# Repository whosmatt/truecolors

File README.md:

> [!CAUTION]
> This is not a manual! This repository serves as documentation only, use at your own risk.

# truecolors

This project captures a lot of embedded approaches I have picked up over the years and serves as my main ESP-IDF reference template for new projects that involve an embedded web UI w/ provisioning and OTA. 

Wide color gamut RGB Laser Mood Light  

I designed this light after growing fascinated with wide color gamut (110% BT.2020) rgb laser projectors. The colors are more vibrant and saturated than anything else. Even the best OLED screens look orange in comparison to the deep red produced by the almost monochromatic lasers.  
I got my hands on a Nichia NUMB12 Laser module, a very common module used in low to mid-tier RGB laser projectors.  
Unfortunately, the module is challenging to drive:
- Common cathode rules out most buck drivers which rely on a cathode shunt
- Forward voltage is very different between the green and red/blue channels
- Laser diodes are much more sensitive to overcurrent than LEDs
- The common cathode has a lower rating than the combined maximum currents, so staggered PWM is required to stay within the ratings

Beyond color gamut, this project also focuses on advanced audio reactive effects. Frustrated with RMS multiband effects, I trained a model to predict the presence and offset of beats in live audio, along with tagging drum hits.  
This allows effects to be completely locked into the tempo of a track rather than responding to volume changes. [truecolors-ml repo](https://github.com/whosmatt/truecolors-ml)

## Safety warning

The laser module used is a class 4 laser, with the output wavelength fully in the visible range. This means that the light has maximum eye damage potential and requires a robust safety protocol to be used safely. Use rated laser safety glasses and a shuttered room when testing without diffusers.

### Diffuser safety

I extensively tested the PLEXIGLAS® LED, Clear 0M200 SC diffuser material to ensure that it doesn't degrade under the intense laser light. Other diffuser materials **did** degrade and even slowly deform under the heat. High transmission is a must to minimize local heating, and the diffuser particles need to be the right size to ensure even diffusion across all three channels. Cheap diffusers may have a insufficient particle size, leading to a partially undiffused red beam passing straight through. Don't assume anything, test everything!

The diffuser design **must** include redundancy to ensure that the detachment/failure of a single diffuser does not compromise eye safety.

All fasteners relevant to eye safety must be secured with thread locker. Consider an additional hardware interlock.

## Hardware design

### PCB

A 4-Layer PCB was designed using Kicad 10. 4 layers were chosed to simplify USB 2.0 impedance and reduce laser driver EMI. Hierarchical design was used to keep the project organized, with Kicad's multichannel feature duplicating the laser driver layout. 

### MCU

An ESP32-S3 was chosen as the main controller for this project. It has plenty of power and the USB2.0 capability simplifies the design.  

ESP-IDF was used as the firmware framework, utilizing the rich scheduling and real-time capabilities of FreeRTOS.  
While most of my other projects rely on PlatformIO for toolchain management, I chose to use the official Espressif path for this to have more direct control over the build process.

### Power supply

USB C PD is used to power the design, with active negotiation to 20V/3A (bootstrapped by hardware and controlled by firmware).

### Laser driver

This design uses a customized constant off-time buck driver using the LM3409 switching converter IC. The design is common for all three channels and current is tuned by a multiturn potentiometer.  
COFT ensures known ripple amplitude, allowing the design to use minimal capacitance while staying safely within the laser's ratings.

Staggered PWM using the ESP32's MCPWM peripheral ensures that no two channels are on at the same time. An optional stretch parameters allows the channels to grow into the unused off time up to 100% combined duty with any color. This allows far higher brightness than with traditional staggered PWM.  
No gap was configured since the common cathode constraint is a thermal one, not an electrical one. 

### Temperature management

A heatpipe based server CPU cooler is used in conjunction with a Honeywell PTM7950 phase change thermal pad to keep the laser module cool.

A fine-adjustable 4-pin PWM server fan allows silent cooling with fine temperature control. This is important because the red laser diode array has a derating both above and below 45°C. The fan is PID controlled via the NTC thermistor located on the laser module.  
The tach signal is fed back to the MCU for fault monitoring. 

### Audio

A MSM261DGT003 PDM MEMS microphone is included for audio reactive effects. Connected to the ESP32's I2S peripheral in PDM mode.

A short recording was analyzed for coil whine cancellation: A single comb filter at the MCPWM frequency as well as a ~48db/oct 4kHz lowpass provided good results and leaves plenty of signal for audio reactive effects.

The first design was quite noisy, these mitigations have been tested and are already in the files:
- Lower noise inductors
  - C22396364 is footprint compatible and advertised as "ultra low buzz noise"
  - Small impact, because MLCC noise is dominant
- No output caps
  - With no output caps noise is reduced to a minimum
    Noise is still significantly audible at 240, 480 Hz. 120 Hz recommended
  - Requires carefully trimming to peak current via scope instead of average current
  - degraded EMI

The following hasn't been tested but is recommended:
- Low noise input caps
  - Murata ZRB: Drop in replacement with ~15dB reduction
  - Next board revision should allow for KRM series with ~25dB reduction

## Software design

### Audio

Core 1 is reserved for audio (including inference) and effect rendering.  

<details>
<summary>Audio pipeline diagram</summary>

```mermaid
flowchart TD
    MIC["PDM mic<br/>I2S RX, 48 kHz"] --> BLK["512-sample block<br/>93.75 blocks/s"]

    subgraph CORE1A["audio task: core 1, prio 5"]
        BLK --> FE["fe_block (frontend v2)<br/>DC block → 4 kHz hi-cut<br/>→ band split → multiband AGC"]
        BLK --> MEL["melflux_block<br/>1024 Hann (previous + current block)<br/>→ FFT → 16 mel bands 150 Hz - 4 kHz<br/>→ log10 → positive flux"]
        FE --> FEOUT["fe_out_t: 12 floats<br/>level, bands[3], rms, flux[3],<br/>fund_rms, mid_flux, treble_flux, spl_db"]
        FEOUT & MEL --> X["x: 28 floats"]

        X --> PA["stage A projection<br/>28 → 12, float"]
        PA --> RA["ring A: 272 blocks × 12"]
        RA --> WA["window: 528 floats<br/>16 fine + 16 mid + 12 coarse<br/>+2 block lookahead"]
        WA --> NNA[["TFLM + esp-nn, int8<br/>stage A 528→128→64 → beat<br/>76k MAC"]]
        NNA --> FB["stage A beat of the<br/>previous block: a[n-3]"]

        X & FB --> PB["stage B projection<br/>29 → 12, float"]
        PB --> RB["ring B: 272 blocks × 12"]
        RB --> WB["window: 528 floats"]
        WB --> NNB[["TFLM + esp-nn, int8<br/>stage B 528→64→32<br/>36k MAC"]]
        NNB --> HEADS["beat, beat_offset, hit[4], music"]

        HEADS -- beat --> TRACK["beattrack<br/>phase accumulator, latches each observation<br/>unlocked: fires on activation ≥ 0.5"]
        HEADS -- beat --> ABUF["tempo ringbuffer: 750 blocks / 8 s"]
        HEADS -- music --> GATE["musicgate<br/>median over ~2 s @ 0.7<br/>+ 3 s hold-off"]
    end

    subgraph CORE1B["estimator task: core 1, prio 3"]
        ABUF --> EST["tempo_estimate every 0.5 s, after ~14 s settle<br/>unbiased autocorr → harmonic sum, fractional lag →<br/>subharmonic → joint period+phase"]
        EST --> HOLD["hold: keep the held grid unless the candidate<br/>refines it, beats its contrast over the last 4 s<br/>by 0.02, or the held contrast drops below 0.03"]
    end

    HOLD -- "period, to_next, contrast<br/>(seqlock observation)" --> TRACK

    TRACK --> FEAT["audio_features_t<br/>level · bands[3] · beat · grid<br/>bpm · kicks · spl_db"]
    FEOUT --> FEAT
    GATE -. "currently debug only" .-> TEL

    FEAT --> FX["effects render task<br/>core 1, prio 18, 90 Hz<br/>reads beat, grid, bands"]
    FX --> LASER["laser_set → MCPWM"]

    HEADS -- *all* --> EVT["EVT_BEATGRID, block rate<br/>kick/snare/hihat/met<br/>act · music · off · err<br/>period · phase · bpm"]
    TRACK --> EVT
    FEAT --> TEL["metrics, 1 Hz<br/>audioDb · bpm<br/>nn.{beat,music,cycles,arena}<br/>nn.gate · nn.track · nn.selftest"]

    subgraph CORE0["core: 0"]
        EVT
        TEL
    end
```

</details> 

## Web UI

The Web UI is based on Svelte 5 and vite, and served as a gzipped static bundle. It is baked into the app partition via CMake's `target_add_binary_data`.  
A websocket endpoint is used to sync the UI state with the firmware, and events are propagated to other connected clients, making the UI multi-user capable.

## Development Environment & Build Instructions

The official Espressif dev container is used and should automatically be detected in VS Code. Build via the status bar, the command palette or just `idf.py build`.  
Build contains all stages, including web.  

### Generating the signing key

OTA updates are signed and require a key to be present in the project directory as `ota_signing_key.pem`.
```bash
source /opt/esp/idf/export.sh
espsecure generate-signing-key --version 2 --scheme rsa3072 ota_signing_key.pem
```

The signature is only checked during OTA updates (wifi).
Secure boot is disabled, no fuses are written. USB flashing/recovery is unaffected.

### Tests

Critical components have unit tests via Unity, run them via `cd test/host && idf.py build && ./build/truecolors_host_tests.elf`.  

### Flashing & Debugging

Access to USB devices from the dev container is a little tricky on windows. 
Refer to the [Espressif documentation](https://docs.espressif.com/projects/vscode-esp-idf-extension/en/latest/additionalfeatures/docker-container.html) for (partially out of date) instructions.  
WSL2 distros commonly don't have USB drivers loaded, so load them via `sudo modprobe cp210x; sudo modprobe ch341; sudo modprobe cdc_acm` in WSL.
The dev container is set up to get access to all ttyACM and ttyUSB class devices.

Flashing via OTA: `curl -X POST --data-binary @build/truecolors.bin http://truecolors.local/api/ota`

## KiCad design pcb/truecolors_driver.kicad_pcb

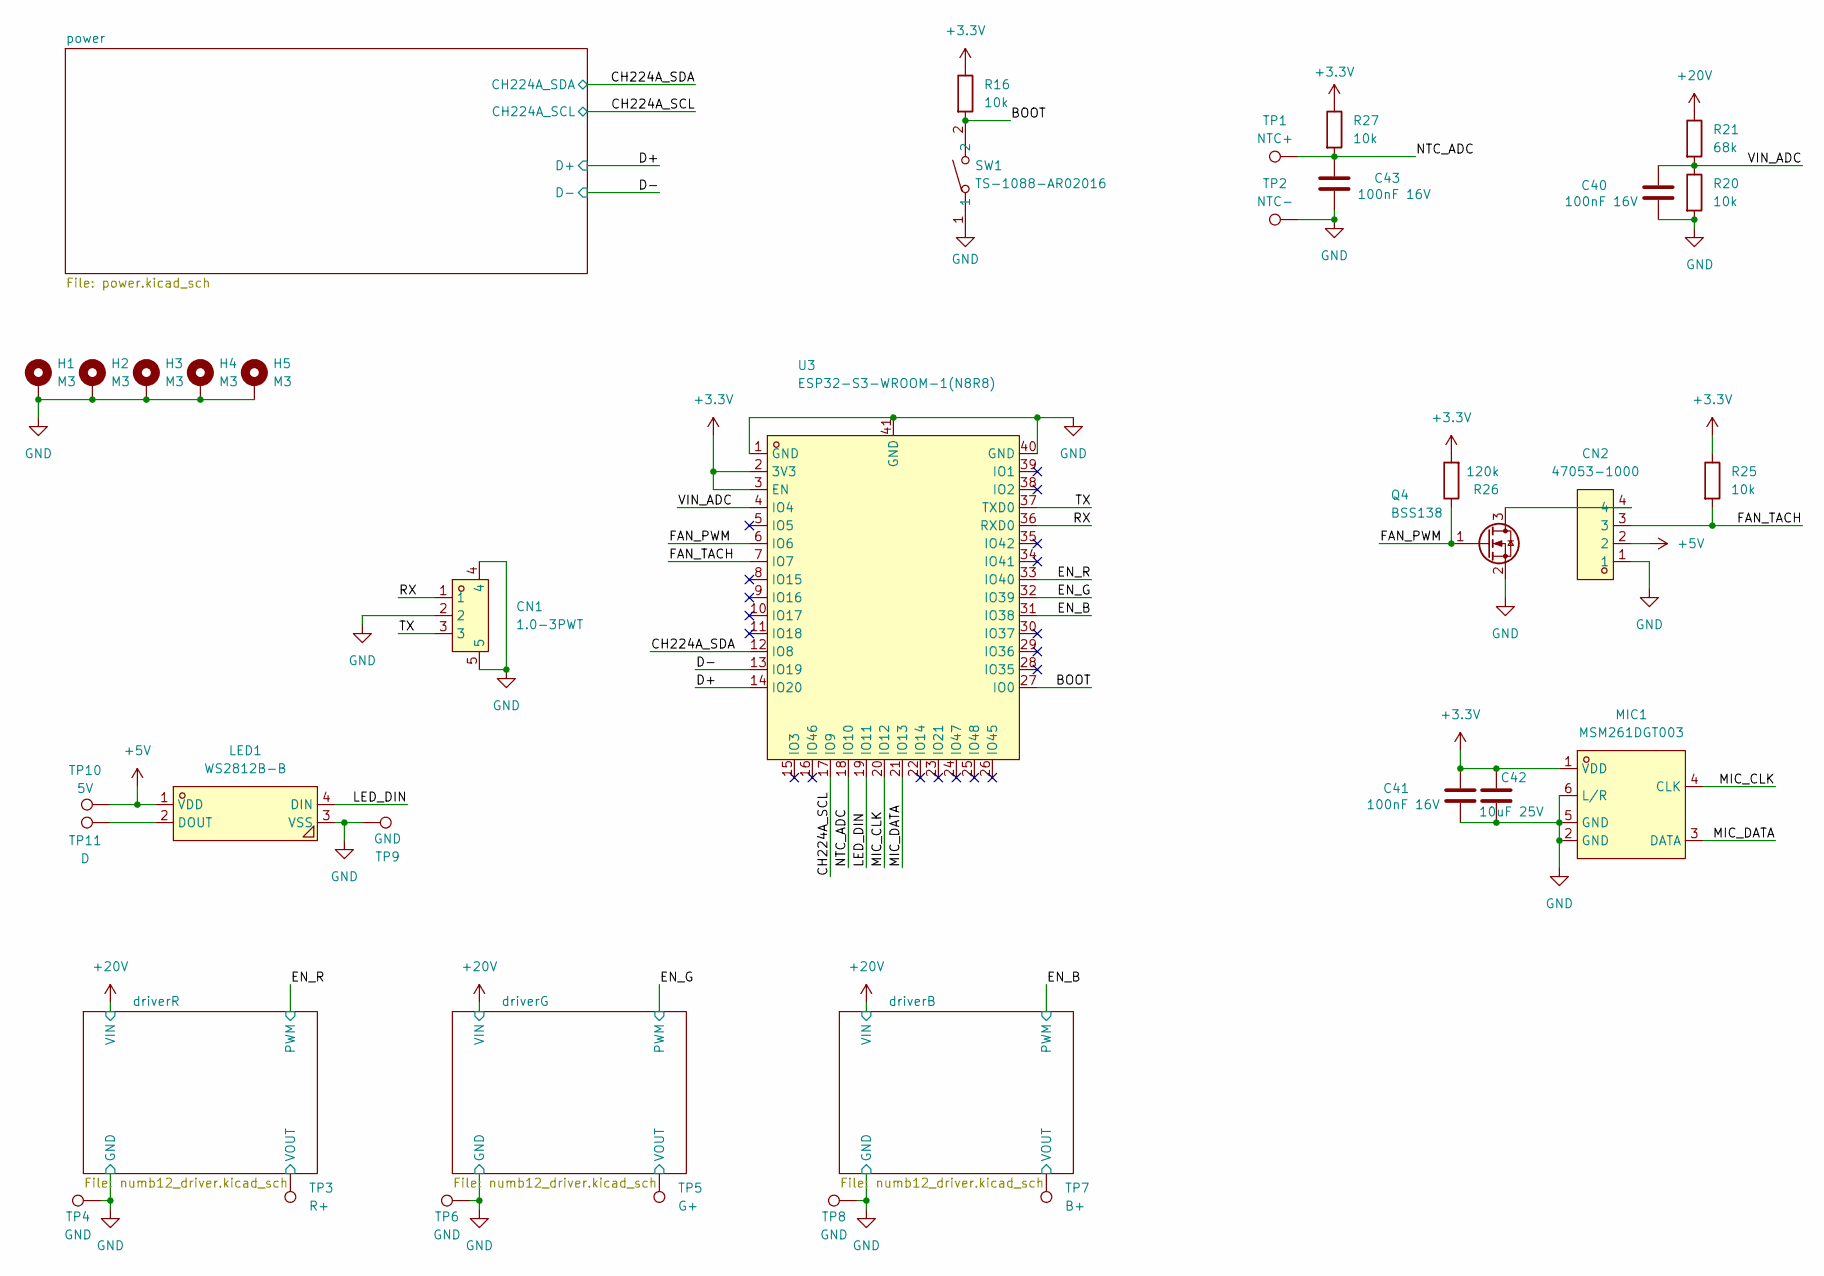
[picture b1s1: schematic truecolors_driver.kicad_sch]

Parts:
C40, C41, C43: 100nF 16V; C_0603_1608Metric; LCSC Part C346192
C42: 10uF 25V; C_0603_1608Metric; LCSC Part C96446
CN1: 1.0-3PWT; CONN-SMD_3P-P1.00_C3029342; MPN 1.0-3PWT; LCSC Part C2763613
CN2: 47053-1000; CONN-TH_47053-1000; MPN 470531000; LCSC Part C240840
H1, H2, H3, H4, H5: M3; MountingHole_3.2mm_M3_DIN965_Pad
LED1: WS2812B-B; LED-SMD_4P-L5.0-W5.0-BL_TC5050RGB; MPN WS2812B-B/W; LCSC Part C114586
MIC1: MSM261DGT003; MIC-SMD_6P-L4.0-W2.0_LMD4020T261-OC3; MPN MSM261DGT003; LCSC Part C48227730
Q4: BSS138; SOT-23; LCSC Part C52895
R16, R20, R25, R27: 10k; R_0603_1608Metric; LCSC Part C2906982
R21: 68k; R_0603_1608Metric; LCSC Part C114633
R26: 120k; R_0603_1608Metric; LCSC Part C2907095
SW1: TS-1088-AR02016; SW-SMD_L3.9-W3.0-P4.45; MPN TS-1088-AR02016; LCSC Part C720477
TP1: NTC+; TestPoint_Keystone_5019_Miniature
TP2: NTC-; TestPoint_Keystone_5019_Miniature
TP3: R+; TestPoint_Keystone_5019_Miniature
TP4, TP6, TP8: GND; TestPoint_Keystone_5019_Miniature
TP5: G+; TestPoint_Keystone_5019_Miniature
TP7: B+; TestPoint_Keystone_5019_Miniature
TP9: GND; TestPoint_Pad_D2.0mm
TP10: 5V; TestPoint_Pad_D2.0mm
TP11: D; TestPoint_Pad_D2.0mm
U3: ESP32-S3-WROOM-1(N8R8); WIRELM-SMD_ESP32-S3-WROOM-1; LCSC Part C2913201

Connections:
+3.3V: C41.2, C42.1, MIC1.1 (VDD), R16.1, R25.1, R26.2, R27.1, U3.2 (3V3), U3.3 (EN); also elsewhere on the board
+5V: CN2.2, LED1.1 (VDD), TP10.1 (1_1); also elsewhere on the board
+20V: R21.1; also elsewhere on the board
/BOOT: R16.2, SW1.2, U3.27 (IO0)
/CH224A_SCL: U3.17 (IO9); also elsewhere on the board
/CH224A_SDA: U3.12 (IO8); also elsewhere on the board
/D+: U3.14 (IO20); also elsewhere on the board
/D-: U3.13 (IO19); also elsewhere on the board
/EN_B: U3.31 (IO38); also elsewhere on the board
/EN_G: U3.32 (IO39); also elsewhere on the board
/EN_R: U3.33 (IO40); also elsewhere on the board
/FAN_PWM: Q4.1 (G), R26.1, U3.6 (IO6)
/FAN_TACH: CN2.3, R25.2, U3.7 (IO7)
/LED_DIN: LED1.4 (DIN), U3.19 (IO11)
/MIC_CLK: MIC1.4 (CLK), U3.20 (IO12)
/MIC_DATA: MIC1.3 (DATA), U3.21 (IO13)
/NTC_ADC: C43.2, R27.2, TP1.1 (1_1), U3.18 (IO10)
/RX: CN1.1, U3.36 (RXD0)
/TX: CN1.3, U3.37 (TXD0)
/VIN_ADC: C40.2, R20.1, R21.2, U3.4 (IO4)
/driverB/VOUT: TP7.1 (1_1); also elsewhere on the board
/driverG/VOUT: TP5.1 (1_1); also elsewhere on the board
/driverR/VOUT: TP3.1 (1_1); also elsewhere on the board
GND: C40.1, C41.1, C42.2, C43.1, CN1.2, CN1.4, CN1.5, CN2.1, H1.1 (1_1), H2.1 (1_1), H3.1 (1_1), H4.1 (1_1), H5.1 (1_1), LED1.3 (VSS), MIC1.2 (GND), MIC1.5 (GND), MIC1.6 (L/R), Q4.2 (S), R20.2, SW1.1, TP2.1 (1_1), TP4.1 (1_1), TP6.1 (1_1), TP8.1 (1_1), TP9.1 (1_1), U3.1 (GND), U3.40 (GND), U3.41 (GND); also elsewhere on the board
unnamed: LED1.2 (DOUT), TP11.1 (1_1)
unnamed: CN2.4, Q4.3 (D)

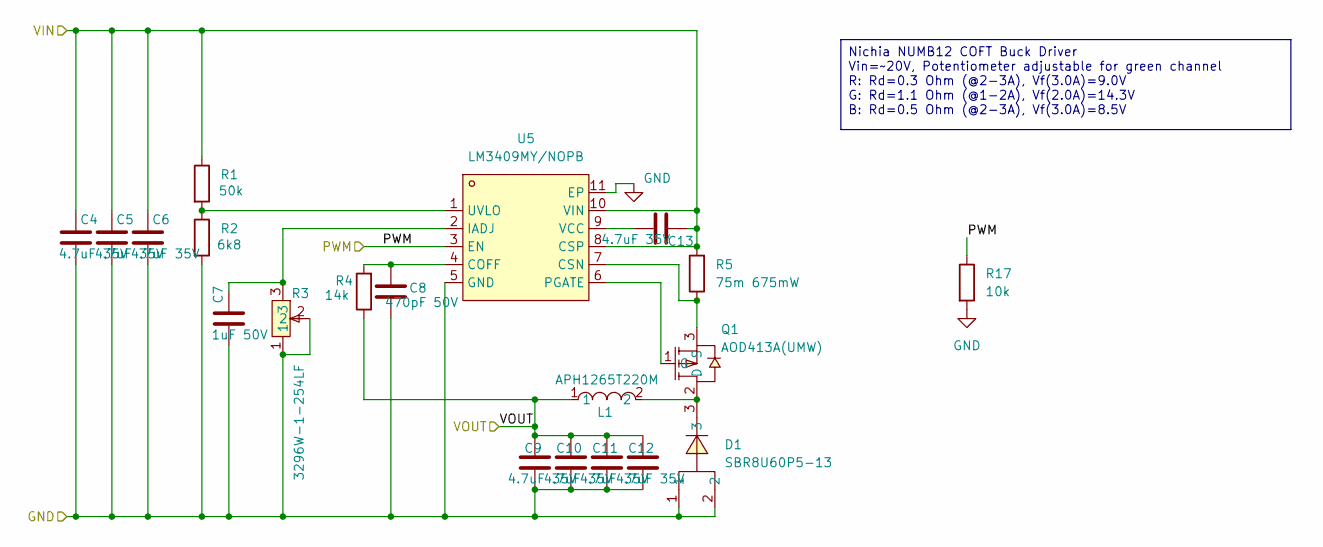
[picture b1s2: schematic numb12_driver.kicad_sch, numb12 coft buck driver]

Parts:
C4, C5, C6, C9, C10, C11, C12, C13: 4.7uF 35V; C_0603_1608Metric; LCSC Part C307467
C7: 1uF 50V; C_0603_1608Metric; LCSC Part C5199872
C8: 470pF 50V; C_0603_1608Metric; LCSC Part C16194503
D1: SBR8U60P5-13; POWERDI-5_L5.4-W4.0-LS6.5-RD-thermal; LCSC Part C154726
L1: APH1265T220M; IND-SMD_L13.5-W12.8_APH1265T; LCSC Part C5349635
Q1: AOD413A(UMW); TO-252-3_L6.6-W6.1-P4.57-LS9.9-BR-CW-thermal; LCSC Part C19100585
R1: 50k; R_0603_1608Metric; LCSC Part C861451
R2: 6k8; R_0603_1608Metric; LCSC Part C2907055
R3: 3296W-1-254LF; RES-ADJ-TH_3296W-clean; LCSC Part C83691
R4: 14k; R_0603_1608Metric; LCSC Part C723488
R5: 75m 675mW; R_1206_3216Metric; LCSC Part C2904225
R17: 10k; R_0603_1608Metric; LCSC Part C2906982
U5: LM3409MY/NOPB; HVSSOP-10_L3.0-W3.0-P0.50-LS4.9-BL-EP-thermal; LCSC Part C527401

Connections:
+20V: C4.1, C5.1, C6.1, C13.1, R1.1, R5.2, U5.8 (CSP), U5.10 (VIN); also elsewhere on the board
/EN_R: R17.1, U5.3 (EN); also elsewhere on the board
/driverR/VOUT: C9.1, C10.1, C11.1, C12.1, L1.1, R4.1; also elsewhere on the board
GND: C4.2, C5.2, C6.2, C7.2, C8.2, C9.2, C10.2, C11.2, C12.2, D1.1, D1.2, R2.2, R3.1, R3.2, R17.2, U5.5 (GND), U5.11 (EP); also elsewhere on the board
unnamed: D1.3, L1.2, Q1.2 (D)
unnamed: Q1.1 (G), U5.6 (PGATE)
unnamed: Q1.3 (S), R5.1, U5.7 (CSN)
unnamed: C8.1, R4.2, U5.4 (COFF)
unnamed: C7.1, R3.3, U5.2 (IADJ)
unnamed: R1.2, R2.1, U5.1 (UVLO)
unnamed: C13.2, U5.9 (VCC)

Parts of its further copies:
C14, C15, C16, C19, C20, C21, C22, C23, C24, C25, C26, C29, C30, C31, C32, C33: 4.7uF 35V; C_0603_1608Metric; LCSC Part C307467
C17, C27: 1uF 50V; C_0603_1608Metric; LCSC Part C5199872
C18, C28: 470pF 50V; C_0603_1608Metric; LCSC Part C16194503
D2, D3: SBR8U60P5-13; POWERDI-5_L5.4-W4.0-LS6.5-RD-thermal; LCSC Part C154726
L2, L3: APH1265T220M; IND-SMD_L13.5-W12.8_APH1265T; LCSC Part C5349635
Q2, Q3: AOD413A(UMW); TO-252-3_L6.6-W6.1-P4.57-LS9.9-BR-CW-thermal; LCSC Part C19100585
R6, R11: 50k; R_0603_1608Metric; LCSC Part C861451
R7, R12: 6k8; R_0603_1608Metric; LCSC Part C2907055
R8, R13: 3296W-1-254LF; RES-ADJ-TH_3296W-clean; LCSC Part C83691
R9, R14: 14k; R_0603_1608Metric; LCSC Part C723488
R10, R15: 75m 675mW; R_1206_3216Metric; LCSC Part C2904225
R18, R19: 10k; R_0603_1608Metric; LCSC Part C2906982
U6, U7: LM3409MY/NOPB; HVSSOP-10_L3.0-W3.0-P0.50-LS4.9-BL-EP-thermal; LCSC Part C527401

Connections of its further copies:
+20V: C14.1, C15.1, C16.1, C23.1, C24.1, C25.1, C26.1, C33.1, R6.1, R10.2, R11.1, R15.2, U6.8 (CSP), U6.10 (VIN), U7.8 (CSP), U7.10 (VIN); also elsewhere on the board
/EN_B: R19.1, U7.3 (EN); also elsewhere on the board
/EN_G: R18.1, U6.3 (EN); also elsewhere on the board
/driverB/VOUT: C29.1, C30.1, C31.1, C32.1, L3.1, R14.1; also elsewhere on the board
/driverG/VOUT: C19.1, C20.1, C21.1, C22.1, L2.1, R9.1; also elsewhere on the board
GND: C14.2, C15.2, C16.2, C17.2, C18.2, C19.2, C20.2, C21.2, C22.2, C24.2, C25.2, C26.2, C27.2, C28.2, C29.2, C30.2, C31.2, C32.2, D2.1, D2.2, D3.1, D3.2, R7.2, R8.1, R8.2, R12.2, R13.1, R13.2, R18.2, R19.2, U6.5 (GND), U6.11 (EP), U7.5 (GND), U7.11 (EP); also elsewhere on the board
unnamed: D2.3, L2.2, Q2.2 (D)
unnamed: Q2.1 (G), U6.6 (PGATE)
unnamed: Q2.3 (S), R10.1, U6.7 (CSN)
unnamed: D3.3, L3.2, Q3.2 (D)
unnamed: Q3.1 (G), U7.6 (PGATE)
unnamed: Q3.3 (S), R15.1, U7.7 (CSN)
unnamed: C18.1, R9.2, U6.4 (COFF)
unnamed: C17.1, R8.3, U6.2 (IADJ)
unnamed: R6.2, R7.1, U6.1 (UVLO)
unnamed: C23.2, U6.9 (VCC)
unnamed: C28.1, R14.2, U7.4 (COFF)
unnamed: C27.1, R13.3, U7.2 (IADJ)
unnamed: R11.2, R12.1, U7.1 (UVLO)
unnamed: C33.2, U7.9 (VCC)

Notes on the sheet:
Nichia NUMB12 COFT Buck Driver Vin=~20V, Potentiometer adjustable for green channel R: Rd=0.3 Ohm (@2-3A), Vf(3.0A)=9.0V G: Rd=1.1 Ohm (@1-2A), Vf(2.0A)=14.3V B: Rd=0.5 Ohm (@2-3A), Vf(3.0A)=8.5V

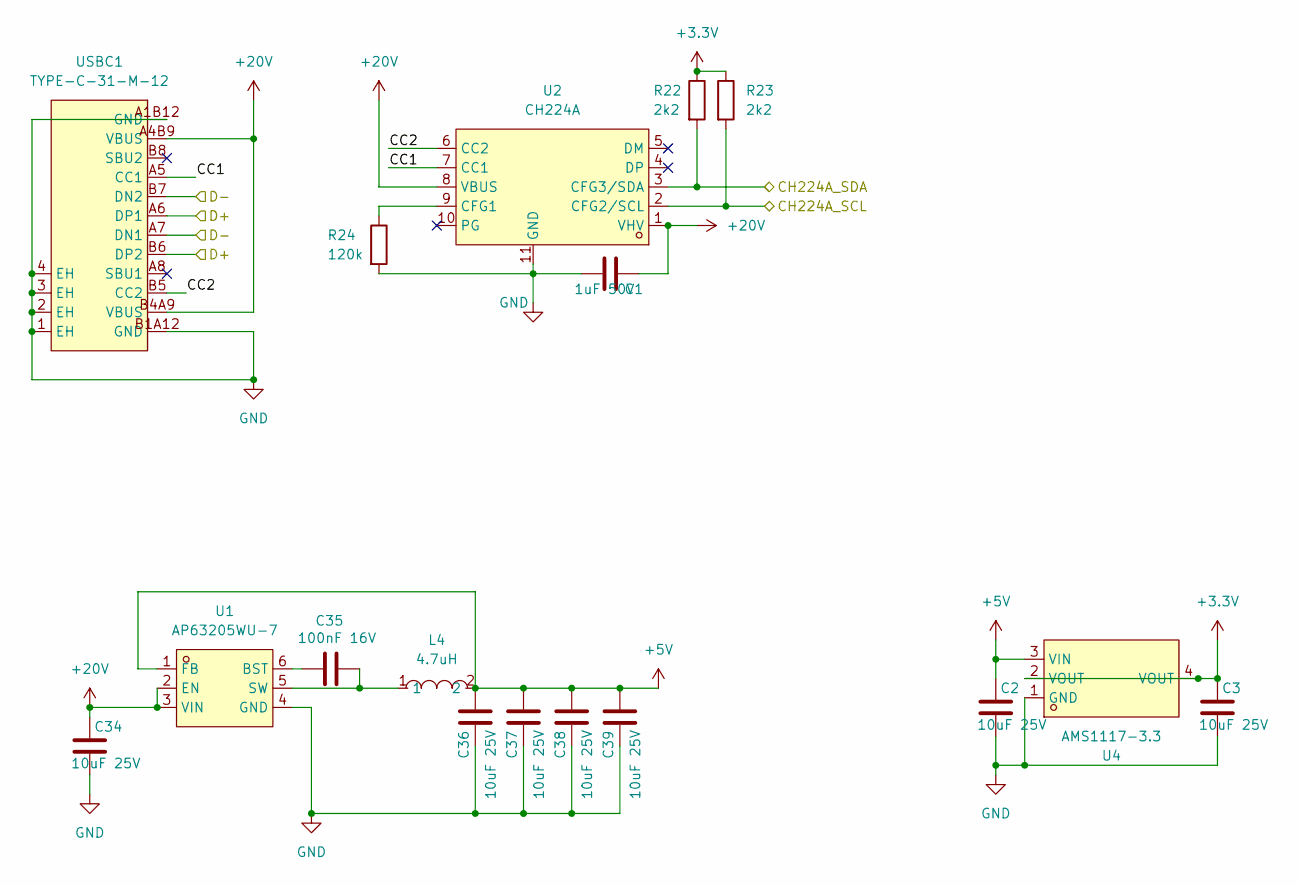
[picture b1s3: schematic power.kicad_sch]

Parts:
C1: 1uF 50V; C_0603_1608Metric; LCSC Part C5199872
C2, C3, C34, C36, C37, C38, C39: 10uF 25V; C_0603_1608Metric; LCSC Part C96446
C35: 100nF 16V; C_0603_1608Metric; LCSC Part C346192
L4: 4.7uH; IND-SMD_L4.4-W4.2; MPN APH0420T4R7M; LCSC Part C5349668
R22, R23: 2k2; R_0603_1608Metric; LCSC Part C2907005
R24: 120k; R_0603_1608Metric; LCSC Part C2907095
U1: AP63205WU-7; TSOT-23-6_L2.9-W1.6-P0.95-LS2.8-BL; MPN AP63205WU-7; LCSC Part C2071056
U2: CH224A; ESSOP-10_L4.9-W3.9-P1.0-LS6.0-TL-EP; LCSC Part C42459160
U4: AMS1117-3.3; SOT-223-3_L6.5-W3.4-P2.30-LS7.0-BR; LCSC Part C6186
USBC1: TYPE-C-31-M-12; USB-C_SMD-TYPE-C-31-M-12_1; LCSC Part C165948

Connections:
+3.3V: C3.1, R22.1, R23.1, U4.2 (VOUT), U4.4 (VOUT); also elsewhere on the board
+5V: C2.1, C36.1, C37.1, C38.1, C39.1, L4.2, U1.1 (FB), U4.3 (VIN); also elsewhere on the board
+20V: C1.1, C34.1, U1.2 (EN), U1.3 (VIN), U2.1 (VHV), U2.8 (VBUS), USBC1.A4B9 (VBUS), USBC1.B4A9 (VBUS); also elsewhere on the board
/CH224A_SCL: R23.2, U2.2 (CFG2/SCL); also elsewhere on the board
/CH224A_SDA: R22.2, U2.3 (CFG3/SDA); also elsewhere on the board
/D+: USBC1.A6 (DP1), USBC1.B6 (DP2); also elsewhere on the board
/D-: USBC1.A7 (DN1), USBC1.B7 (DN2); also elsewhere on the board
/power/CC1: U2.7 (CC1), USBC1.A5 (CC1)
/power/CC2: U2.6 (CC2), USBC1.B5 (CC2)
GND: C1.2, C2.2, C3.2, C34.2, C36.2, C37.2, C38.2, C39.2, R24.2, U1.4 (GND), U2.11 (GND), U4.1 (GND), USBC1.1 (EH), USBC1.2 (EH), USBC1.3 (EH), USBC1.4 (EH), USBC1.A1B12 (GND), USBC1.B1A12 (GND); also elsewhere on the board
unnamed: C35.1, U1.6 (BST)
unnamed: C35.2, L4.1, U1.5 (SW)
unnamed: R24.1, U2.9 (CFG1)

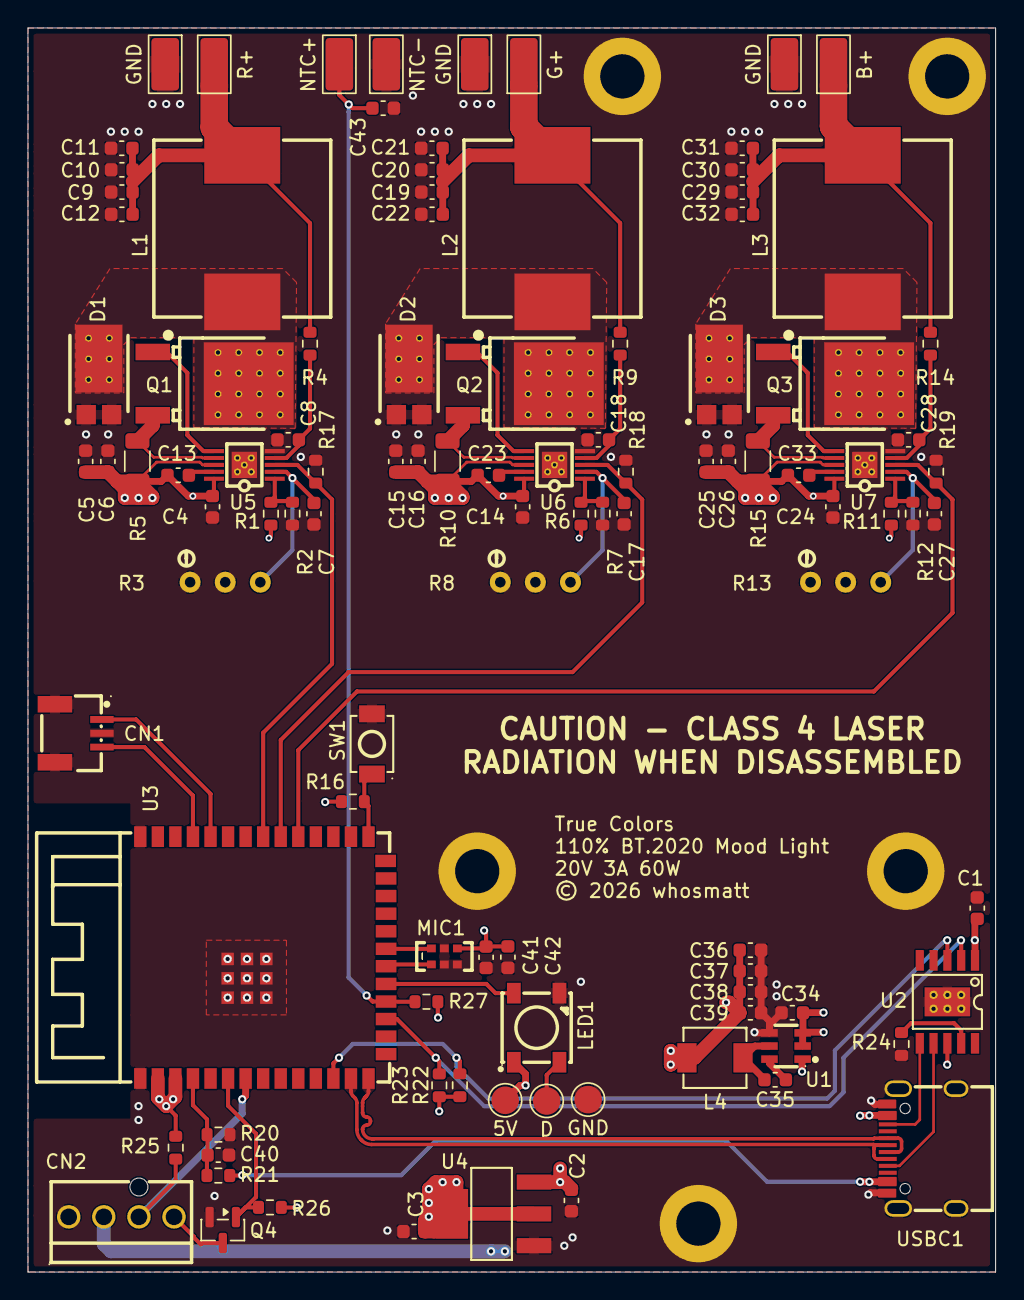
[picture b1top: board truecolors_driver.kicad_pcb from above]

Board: 4 copper layers, 70.0 x 90.0 mm, 110 parts (0 on the bottom side), 52 nets.

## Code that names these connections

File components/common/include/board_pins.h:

// board_pins.h

#pragma once

#include "driver/gpio.h"

// ---------------------------------------------------------------------------
// GPIO map (ESP32-S3-WROOM-1 N8R8)
// ---------------------------------------------------------------------------
// Laser enables, active-high to the LM3409 EN/PWM input.
// Each net has a 10k pulldown so lasers stay off while the GPIO is Hi-Z.
#define PIN_EN_R        GPIO_NUM_40   // MCPWM operator 0 -> driverR
#define PIN_EN_G        GPIO_NUM_39   // MCPWM operator 1 -> driverG
#define PIN_EN_B        GPIO_NUM_38   // MCPWM operator 2 -> driverB

// Fan (5 V 4-wire PC fan via low-side BSS138).
#define PIN_FAN_PWM     GPIO_NUM_6    // LEDC, 25 kHz, output_invert=1
#define PIN_FAN_TACH    GPIO_NUM_7    // PCNT, open-collector, 10k pull-up to 3.3 V

// CH224A USB-PD sink (I2C master).
#define PIN_I2C_SDA     GPIO_NUM_8    // 2.2k pull-up to 3.3 V
#define PIN_I2C_SCL     GPIO_NUM_9    // 2.2k pull-up to 3.3 V

// Analog sense on ADC1. ADC2 is unusable while Wi-Fi is active.
#define PIN_VIN_ADC     GPIO_NUM_4    // ADC1_CH3, 20 V rail via 68k/10k divider
#define PIN_NTC_ADC     GPIO_NUM_10   // ADC1_CH9, laser-module NTC via 10k/NTC divider

// PDM MEMS microphone (MSM261DGT003).
#define PIN_MIC_CLK     GPIO_NUM_12   // I2S PDM CLK
#define PIN_MIC_DATA    GPIO_NUM_13   // I2S PDM DATA (RX)

// WS2812B-B status LED.
#define PIN_LED_DATA    GPIO_NUM_11   // RMT TX (led_strip)

// User button / boot strap (SW1 + 10k pull-up to 3.3 V).
// Boot strap at reset; free to read as a button once running.
#define PIN_BTN         GPIO_NUM_0

// ---------------------------------------------------------------------------
// Peripheral-unit allocation
// ---------------------------------------------------------------------------
// MCPWM: one group, one timer, three operators.
#define MCPWM_GROUP_ID      0
#define MCPWM_TIMER_ID      0
#define MCPWM_OPER_R        0
#define MCPWM_OPER_G        1
#define MCPWM_OPER_B        2

// LEDC fan PWM.
#define LEDC_FAN_MODE       LEDC_LOW_SPEED_MODE
#define LEDC_FAN_TIMER      LEDC_TIMER_0
#define LEDC_FAN_CHANNEL    LEDC_CHANNEL_0

// PCNT fan tach.
#define PCNT_FAN_UNIT_ID    0

// I2C CH224A bus.
#define I2C_PORT_CH224A     0

// I2S PDM RX microphone.
#define I2S_PORT_MIC        0

// ADC sense channels on ADC1.
#define ADC_UNIT_SENSE      ADC_UNIT_1
#define ADC_CH_VIN          ADC_CHANNEL_3   // GPIO4
#define ADC_CH_NTC          ADC_CHANNEL_9   // GPIO10

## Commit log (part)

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2026-06-13 add pcb
2026-06-13 add .gitignore
2026-06-13 add numb12 datasheet
2026-06-13 add doc
2026-06-13 update pcb
2026-06-13 add slopdoc
2026-06-13 R26 pullup instead of pulldown for fan-off boot
2026-06-14 add mic doc
2026-06-14 fix via size
2026-06-14 add mic, add ntc, fix all drc errors
2026-06-14 update doc
2026-06-14 refactor schematic
2026-06-14 add mounting holes, labels
2026-06-14 finalize bom
2026-06-14 fix missing labels
2026-06-14 add status led
2026-06-14 update bom
2026-06-16 generate ESP-IDF devcontainer
2026-06-16 add node
2026-06-16 pin container
2026-06-16 fix line endings :)
2026-06-17 fix typo
2026-06-18 update gitignore
2026-06-18 init idf project, init deps, init components
2026-06-18 implement appstate, NVS
2026-06-18 clean up comments
2026-06-18 implement core laser driver
2026-06-18 implement effects engine, starter effects
2026-06-18 implement sysmgr, safety state machine, fan control
2026-06-18 implement wifi manager, http server, websocket protocol
2026-06-18 implement svelte web ui
2026-06-18 embed gzipped web ui, add ota endpoint
2026-06-19 implement audio pdm rx, level and beat features
2026-06-19 fix cie mapping, rgb gradients, status layout; add cie axes and gradient
2026-06-19 move connection dot to telemetry header, drop status label
2026-06-19 gate network admin actions behind a confirm modal
2026-06-19 add srgb reference gamut to cie chart
2026-06-19 disable text selection on cie chart drag
2026-06-19 lowercase brand name in ui
2026-06-19 update cie chart style
2026-06-19 update footer
2026-06-19 add IS_SANDBOX
2026-06-20 UI overhaul
2026-06-20 add mechanical files
2026-06-20 add MIT license
2026-06-20 add README
2026-06-23 update devcontainer: usb support
2026-06-23 usb in containers is a miserable experience (huge news)
2026-06-24 drop udev and just mount dev instead, drop privileged and add cgroup rules
2026-06-24 fix esp32 mcu temp sensor readout
2026-06-24 implement full OTA updater
2026-06-24 fix wifi only connecting after reboot
2026-06-24 add captive portal to AP mode
2026-06-24 fix: ws events not reaching other clients
2026-06-28 add rainbow, rainbow_window, discombobulate effects
2026-06-28 pin esp-idf to 6.0.1, set WDT explicitly since this idf version lowers the default

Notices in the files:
pcb/truecolors_driver.kicad_pcb:
© 2026 whosmatt
